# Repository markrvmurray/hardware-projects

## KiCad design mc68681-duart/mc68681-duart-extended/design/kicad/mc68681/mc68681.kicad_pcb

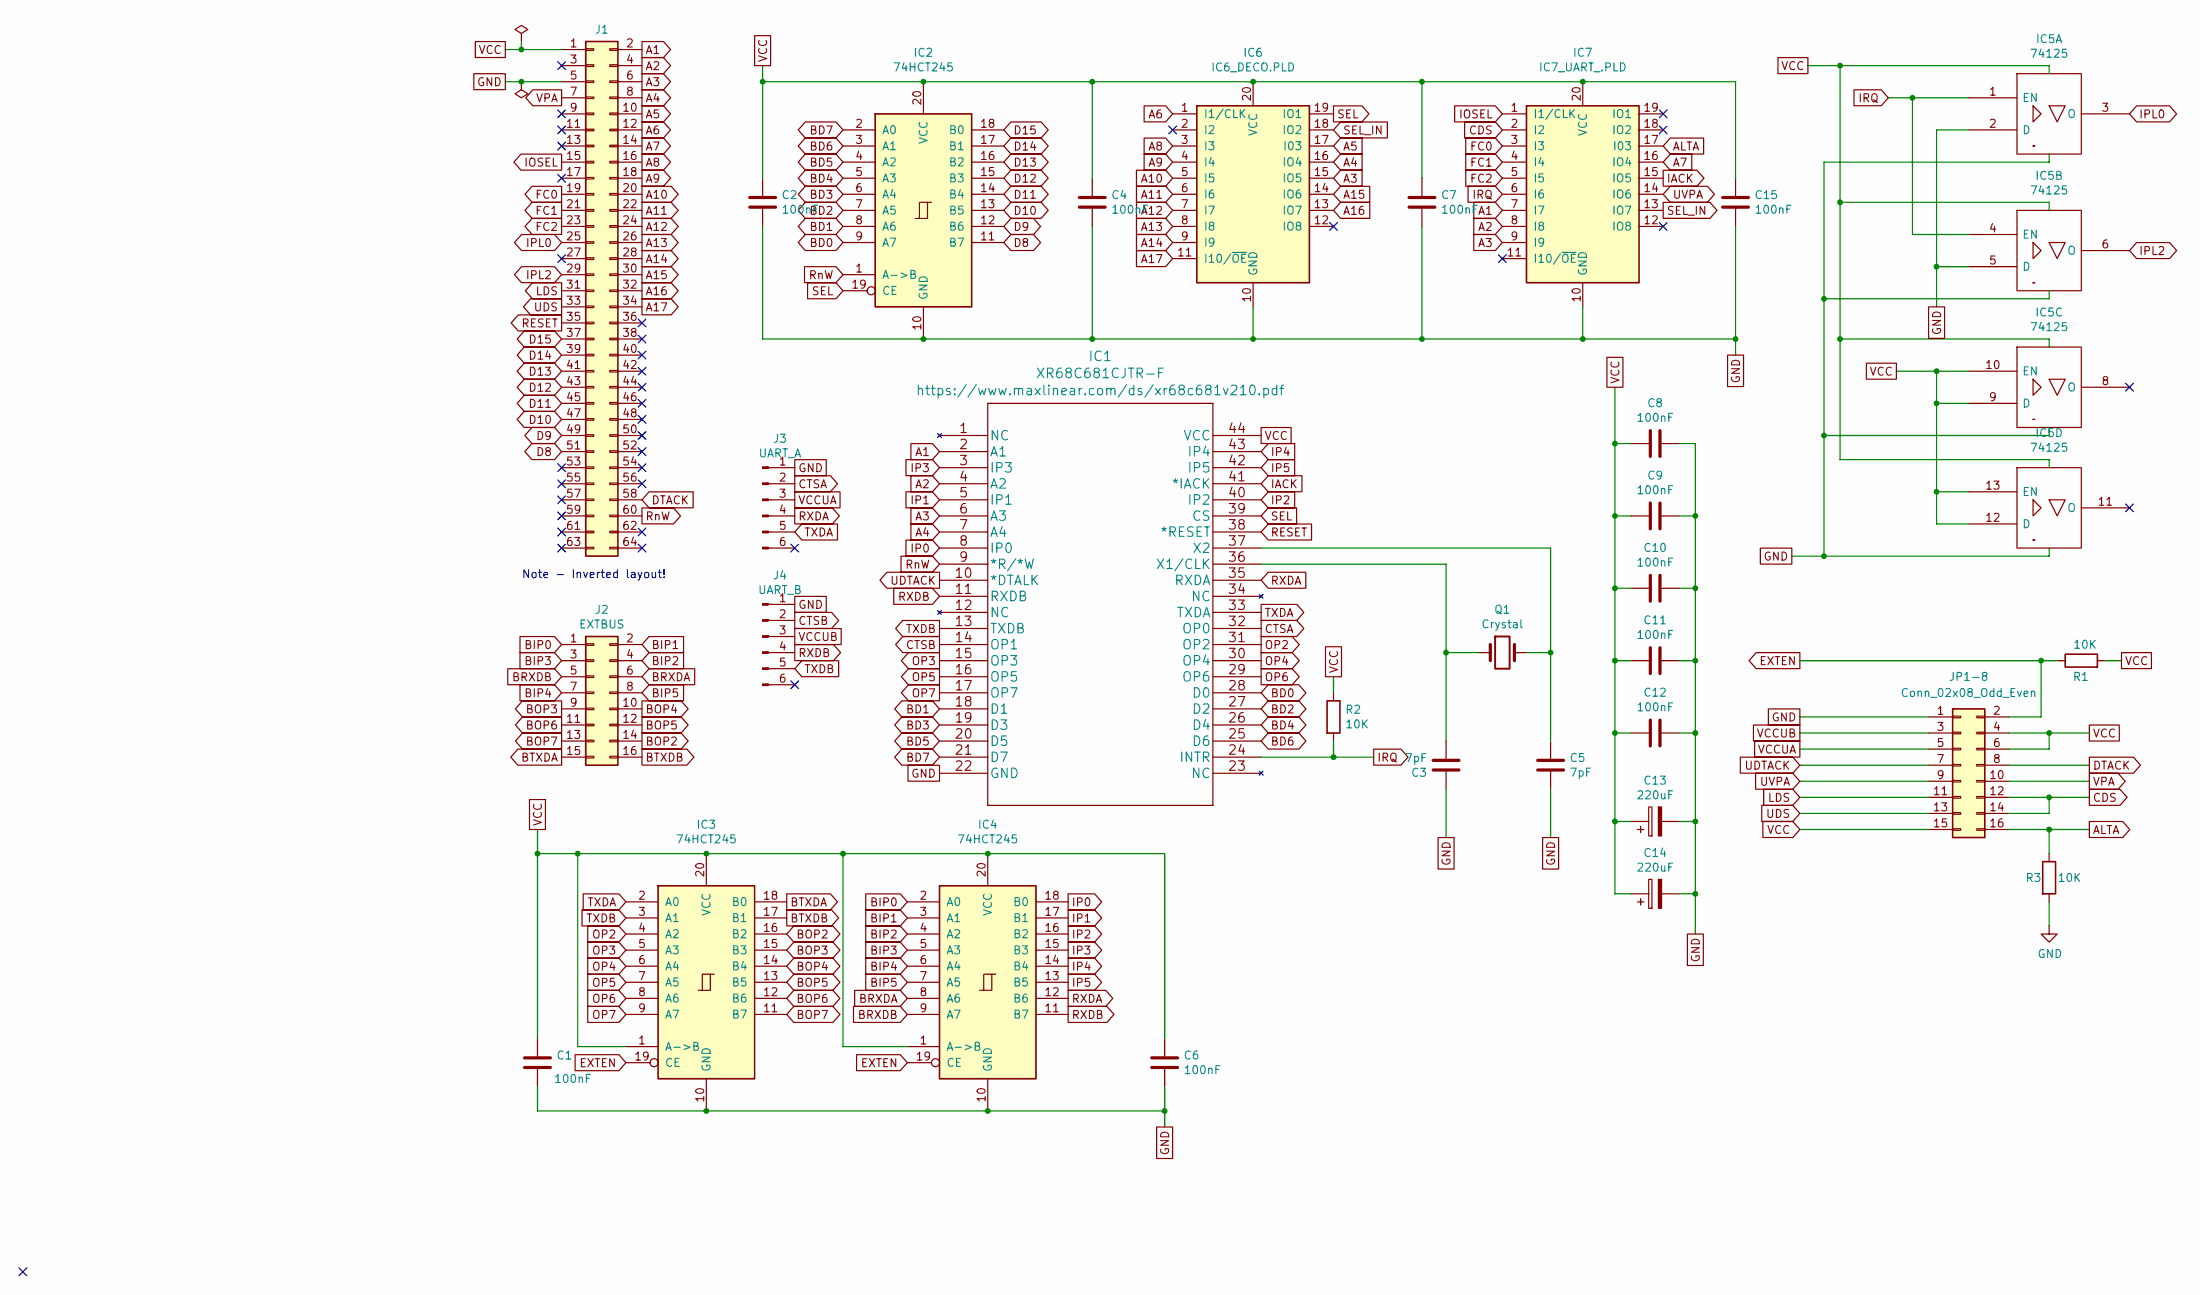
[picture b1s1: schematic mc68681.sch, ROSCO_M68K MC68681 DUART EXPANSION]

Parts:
C1, C2, C4, C6, C7, C8, C9, C10, C11, C12, C15: 100nF; C2.5-3
C3, C5: 7pF; C_Rect_L7.0mm_W2.0mm_P5.00mm
C13, C14: 220uF; CP_Radial_D6.3mm_P2.50mm
IC1: XR68C681CJTR-F; PLCC-44_THT-Socket
IC2, IC3, IC4: 74HCT245; DIP-20_W7.62mm_Socket_LongPads
IC5: 74125; DIP-14_W7.62mm_Socket_LongPads
IC6: IC6_DECO.PLD; DIP-20_W7.62mm_Socket_LongPads
IC7: IC7_UART_.PLD; DIP-20_W7.62mm_Socket_LongPads
J1: Conn_02x32_Odd_Even; PinHeader_2x32_P2.54mm_Vertical
J2: EXTBUS; PinHeader_2x08_P2.54mm_Vertical
J3: UART_A; PinHeader_1x06_P2.54mm_Vertical
J4: UART_B; PinHeader_1x06_P2.54mm_Vertical
JP1-8: Conn_02x08_Odd_Even; PinHeader_2x08_P2.54mm_Vertical
Q1: Crystal; Crystal_HC49-4H_Vertical
R1, R2, R3: 10K; R_Axial_DIN0207_L6.3mm_D2.5mm_P10.16mm_Horizontal

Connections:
A1: IC1.2 (A1), IC7.7 (I7), J1.2
A2: IC1.4 (A2), IC7.8 (I8), J1.4
A3: IC1.6 (A3), IC6.15 (IO5), IC7.9 (I9), J1.6
A4: IC1.7 (A4), IC6.16 (IO4), J1.8
A5: IC6.17 (I03), J1.10
A6: IC6.1 (I1/CLK), J1.12
A7: IC7.16 (IO4), J1.14
A8: IC6.3 (I3), J1.16
A9: IC6.4 (I4), J1.18
A10: IC6.5 (I5), J1.20
A11: IC6.6 (I6), J1.22
A12: IC6.7 (I7), J1.24
A13: IC6.8 (I8), J1.26
A14: IC6.9 (I9), J1.28
A15: IC6.14 (IO6), J1.30
A16: IC6.13 (IO7), J1.32
A17: IC6.11 (I10/~OE~), J1.34
ALTA: IC7.17 (I03), JP1-8.16, R3.1
BD0: IC1.28 (D0), IC2.9 (A7)
BD1: IC1.18 (D1), IC2.8 (A6)
BD2: IC1.27 (D2), IC2.7 (A5)
BD3: IC1.19 (D3), IC2.6 (A4)
BD4: IC1.26 (D4), IC2.5 (A3)
BD5: IC1.20 (D5), IC2.4 (A2)
BD6: IC1.25 (D6), IC2.3 (A1)
BD7: IC1.21 (D7), IC2.2 (A0)
BIP0: IC4.2 (A0), J2.1
BIP1: IC4.3 (A1), J2.2
BIP2: IC4.4 (A2), J2.4
BIP3: IC4.5 (A3), J2.3
BIP4: IC4.6 (A4), J2.7
BIP5: IC4.7 (A5), J2.8
BOP2: IC3.16 (B2), J2.14
BOP3: IC3.15 (B3), J2.9
BOP4: IC3.14 (B4), J2.10
BOP5: IC3.13 (B5), J2.12
BOP6: IC3.12 (B6), J2.11
BOP7: IC3.11 (B7), J2.13
BRXDA: IC4.8 (A6), J2.6
BRXDB: IC4.9 (A7), J2.5
BTXDA: IC3.18 (B0), J2.15
BTXDB: IC3.17 (B1), J2.16
CDS: IC7.2 (I2), JP1-8.12, JP1-8.14
CTSA: IC1.32 (OP0), J3.2
CTSB: IC1.14 (OP1), J4.2
D8: IC2.11 (B7), J1.51
D9: IC2.12 (B6), J1.49
D10: IC2.13 (B5), J1.47
D11: IC2.14 (B4), J1.45
D12: IC2.15 (B3), J1.43
D13: IC2.16 (B2), J1.41
D14: IC2.17 (B1), J1.39
D15: IC2.18 (B0), J1.37
DTACK: J1.58, JP1-8.8
EXTEN: IC3.19 (CE), IC4.19 (CE), JP1-8.2, R1.1
FC0: IC7.3 (I3), J1.19
FC1: IC7.4 (I4), J1.21
FC2: IC7.5 (I5), J1.23
IACK: IC1.41 (*IACK), IC7.15 (IO5)
IOSEL: IC7.1 (I1/CLK), J1.15
IP0: IC1.8 (IP0), IC4.18 (B0)
IP1: IC1.5 (IP1), IC4.17 (B1)
IP2: IC1.40 (IP2), IC4.16 (B2)
IP3: IC1.3 (IP3), IC4.15 (B3)
IP4: IC1.43 (IP4), IC4.14 (B4)
IP5: IC1.42 (IP5), IC4.13 (B5)
IPL0: IC5.3 (O), J1.25
IPL2: IC5.6 (O), J1.29
IRQ: IC1.24 (INTR), IC5.1 (EN), IC5.4 (EN), IC7.6 (I6), R2.2
LDS: J1.31, JP1-8.11
unnamed: C3.2, IC1.36 (X1/CLK), Q1.1
unnamed: C5.1, IC1.37 (X2), Q1.2
OP2: IC1.31 (OP2), IC3.4 (A2)
OP3: IC1.15 (OP3), IC3.5 (A3)
OP4: IC1.30 (OP4), IC3.6 (A4)
OP5: IC1.16 (OP5), IC3.7 (A5)
OP6: IC1.29 (OP6), IC3.8 (A6)
OP7: IC1.17 (OP7), IC3.9 (A7)
RESET: IC1.38 (*RESET), J1.35
RXDA: IC1.35 (RXDA), IC4.12 (B6), J3.4
RXDB: IC1.11 (RXDB), IC4.11 (B7), J4.4
RnW: IC1.9 (*R/*W), IC2.1 (A->B), J1.60
SEL: IC1.39 (CS), IC2.19 (CE), IC6.19 (IO1)
SEL_IN: IC6.18 (IO2), IC7.13 (IO7)
TXDA: IC1.33 (TXDA), IC3.2 (A0), J3.5
TXDB: IC1.13 (TXDB), IC3.3 (A1), J4.5
UDS: J1.33, JP1-8.13
UDTACK: IC1.10 (*DTALK), JP1-8.7
UVPA: IC7.14 (IO6), JP1-8.9
VCCUA: J3.3, JP1-8.5
VCCUB: J4.3, JP1-8.3
VPA: J1.7, JP1-8.10

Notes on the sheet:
Note - Inverted layout!

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
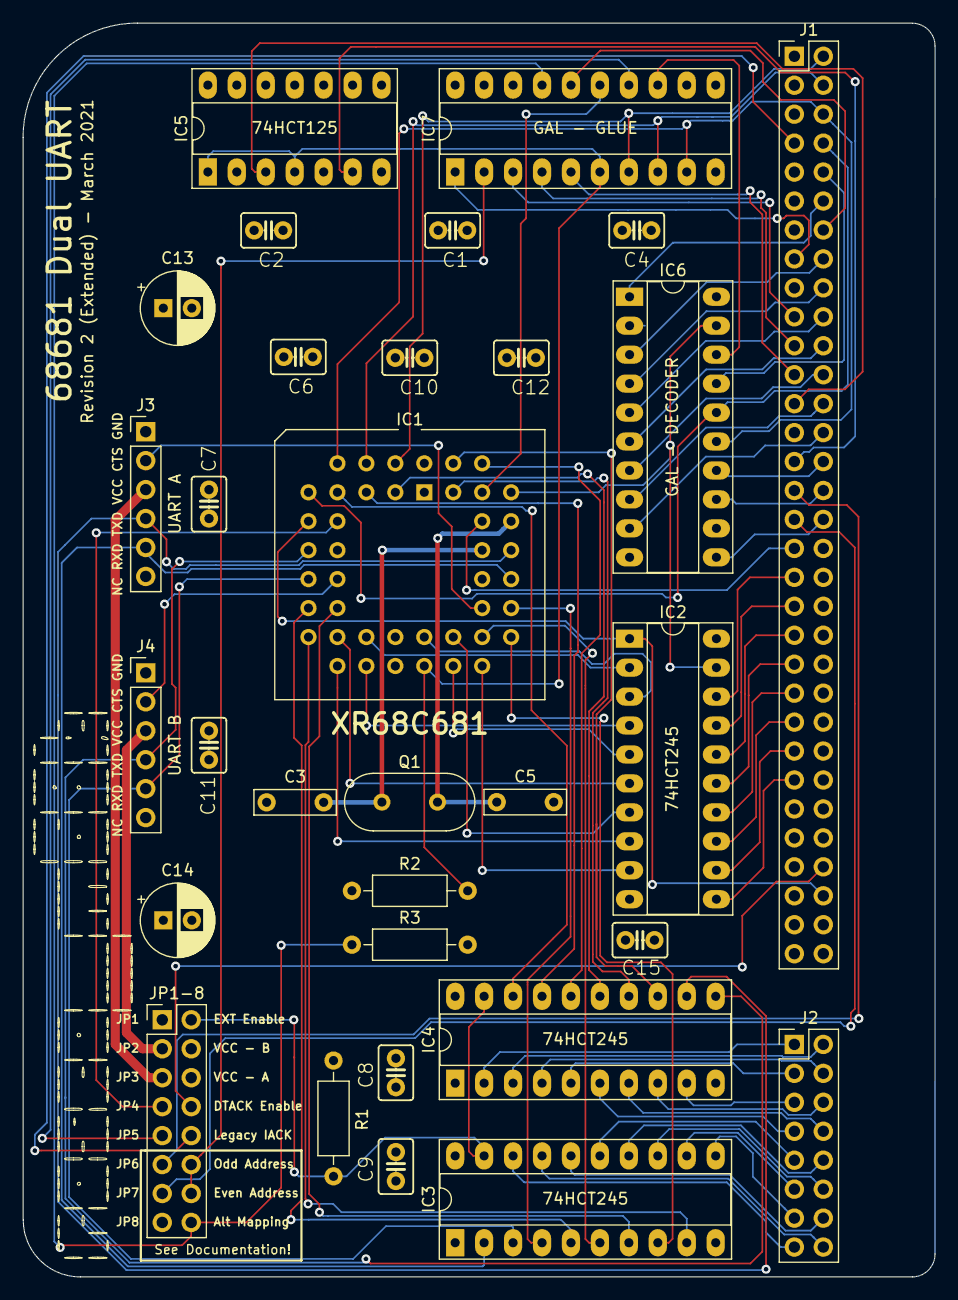
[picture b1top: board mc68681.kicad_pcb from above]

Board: 4 copper layers, 80.0 x 110.0 mm, 31 parts (0 on the bottom side), 94 nets.

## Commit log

2020-12-13 Add initial Xosera design and GAL code
2020-12-13 Remove misleading comment
2021-03-01 Initial work on schematic, board ripped up
2021-03-01 First cut redo 68681 layout, add lib and pretty
2021-03-01 PDF updated
2021-03-01 Fix 7pF footprint & prep for prototype fab
2021-03-02 Fix incorrect gerber zip
2021-03-10 Adjust layout ready for extended board
2021-03-10 Update glue logic for new board
2021-03-13 Change r2 base address
2021-03-13 Add r2x board
2021-03-13 Glue updated and silkscreen fixed
2021-03-13 Update for new r2 base address

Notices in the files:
mc68681-duart/mc68681-duart-extended/design/kicad/mc68681/mc68681.kicad_pcb:
Copyright ©2021 Ross Bamford & Contributors
mc68681-duart/mc68681-duart-extended/design/kicad/mc68681/mc68681.sch:
Open Source Hardware licenced under CERN Open Hardware Licence
Copyright ©2020-2021 Ross Bamford and Contributors
